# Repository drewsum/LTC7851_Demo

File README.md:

# LTC7851_Demo
Demo board for testing LTC7851 Quad Phase Buck Converter
KiCAD V5.0.0

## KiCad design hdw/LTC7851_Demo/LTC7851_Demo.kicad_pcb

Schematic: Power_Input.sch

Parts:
C201, C207: 0.1uF; C_0603; Voltage 50V; Digi-Key PN 490-4779-1-ND
C202, C205: 10nF; C_0603; Voltage 50V; Digi-Key PN 1276-1921-1-ND
C203: 1nF; C_0603; Voltage 50V; Digi-Key PN 311-1080-1-ND
C204, C206, C208: 100uF; CP_Tantalum_Case-X_EIA-7343-43_Reflow; Voltage 16V; Tolerance 10%; Digi-Key PN 718-1102-1-ND
D201: 24V; D_SMA; Digi-Key PN SMAJ24CALFCT-ND
D202: Green; LED_0603; Digi-Key PN 160-1446-1-ND
F201, F202: 25A; Fuse_SMD1206_Reflow; Digi-Key PN 507-1946-1-ND
J201: +12V IN; Wuerth_7461096_M4_Shank_9pos; Digi-Key PN 732-3214-ND
J206: GND IN; Wuerth_7461096_M4_Shank_9pos; Digi-Key PN 732-3214-ND
Q201, Q202: BSC123N10LSGATMA1; TDSON-8-1; Digi-Key PN BSC123N10LSGATMA1CT-ND
R201: 6.04M; R_0603; Tolerance 1%; Digi-Key PN 541-6.04MHCT-ND
R202: 86.6k; R_0603; Tolerance 1%; Digi-Key PN 311-86.6KHRCT-ND
R203: 243k; R_0603; Tolerance 1%; Digi-Key PN 541-243KHCT-ND
R204: 100k; R_0603; Tolerance 1%; Digi-Key PN P100KHCT-ND
R205, R206: 10; R_0603; Tolerance 1%; Digi-Key PN YAG3351CT-ND
R207: 10k; R_0603; Tolerance 1%; Digi-Key PN RHM10KADCT-ND
R208: 5.1k; R_0603; Tolerance 1%; Digi-Key PN RMCF0603FT5K10CT-ND
R209: 1k; R_0603; Tolerance 1%; Digi-Key PN RHM1.0KDCT-ND
TP201: TP; Pin_Header_Angled_1x01_Pitch2.54mm
TP202: TP; Measurement_Point_Round-SMD-Pad_Small
U201: LTC4365DDB; DFN-8-1EP_2x3mm_Pitch0.5mm; Digi-Key PN LTC4365IDDB#TRMPBFCT-ND
U202: 74LVC1G06; SOT-353_SC-70-5; Digi-Key PN 296-8484-1-ND

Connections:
+5.5V_MNG: C207.1, D202.2, R207.1, U202.5; also elsewhere on the board
+12V: C204.1, C206.1, C208.1, Q202.5 (D), TP202.1, U201.6; also elsewhere on the board
+12Vin: C201.1, C202.1, C203.1, D201.1, J201.1, Q201.5 (D), R201.1, R204.1, U201.4
GND: C201.2, C202.2, C203.2, C204.2, C205.2, C206.2, C207.2, C208.2, D201.2, J206.1, R203.2, TP201.1, U201.1, U201.9, U202.3; also elsewhere on the board
unnamed: C205.1, R208.2
unnamed: D202.1, R209.1
unnamed: Q201.1 (S), Q201.2 (S), Q201.3 (S), Q202.1 (S), Q202.2 (S), Q202.3 (S)
unnamed: Q201.4 (G), R205.2
unnamed: Q202.4 (G), R206.1
unnamed: R201.2, R202.1, U201.3
unnamed: R202.2, R203.1, U201.2
unnamed: R204.2, U201.8
unnamed: R205.1, R206.2, R208.1, U201.5
unnamed: R209.2, U202.4
POS12_PGOOD: R207.2, U201.7, U202.2

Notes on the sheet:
Power Input

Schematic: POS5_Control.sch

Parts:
C301, C302, C303, C304, C305: 0.1uF; C_0603; Voltage 50V; Digi-Key PN 490-4779-1-ND
D301: Red; LED_0603; Digi-Key PN 160-1447-1-ND
D302, D303: Green; LED_0603; Digi-Key PN 160-1446-1-ND
J301: CLKOUT; Pin_Header_Straight_1x02_Pitch2.54mm
J302: RUN; Pin_Header_Straight_1x03_Pitch2.54mm
J304: IAVG; Pin_Header_Straight_1x02_Pitch2.54mm
R301: 0; R_0603; Tolerance 1%; Digi-Key PN 311-0.0GRCT-ND
R302: 2; R_0603; Tolerance 1%; Digi-Key PN RMCF0603FT2R00CT-ND
R303: 51.1k; R_0603; Tolerance 1%; Digi-Key PN P51.1KHCT-ND
R304, R305, R310: 10k; R_0603; Tolerance 1%; Digi-Key PN RHM10KADCT-ND
R306, R307, R308: 1k; R_0603; Tolerance 1%; Digi-Key PN RHM1.0KDCT-ND
U301: LTC7851UHH; QFN-58-1EP_9x5mm_Pitch0.4mm; Digi-Key PN LTC7851IUHH#PBF-ND
U302: 74LVC1G17; SOT-353_SC-70-5; Digi-Key PN 296-11934-1-ND
U303, U304: 74LVC1G06; SOT-353_SC-70-5; Digi-Key PN 296-8484-1-ND

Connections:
+5.5V_MNG: C303.1, C304.1, C305.1, D301.2, D302.2, D303.2, J302.1, R301.1, R304.1, R305.1, U302.5, U303.5, U304.5; also elsewhere on the board
+12V: R302.1; also elsewhere on the board
/POS5 Phase 1/POS5_ISNS1_-: U301.45; also elsewhere on the board
/POS5 Phase 1/POS5_VSNSO1_-: U301.3; also elsewhere on the board
/POS5 Phase 2/POS5_ISNS2_-: U301.44; also elsewhere on the board
/POS5 Phase 3/POS5_ISNS3_-: U301.33; also elsewhere on the board
/POS5 Phase 4/POS5_ISNS4_-: U301.32; also elsewhere on the board
GND: C301.2, C302.2, C303.2, C304.2, C305.2, J301.2, J302.3, J304.2, R303.2, R310.2, U301.5, U301.59, U302.3, U303.3, U304.3; also elsewhere on the board
unnamed: C302.1, R302.2, U301.39
unnamed 21: U301.58; also elsewhere on the board
unnamed 25: U301.46; also elsewhere on the board
unnamed 29: U301.43; also elsewhere on the board
unnamed 33: U301.34; also elsewhere on the board
unnamed 37: U301.31; also elsewhere on the board
unnamed: D301.1, R306.1
unnamed: D302.1, R307.1
unnamed: D303.1, R308.1
unnamed: J301.1, U301.54
unnamed: R303.1, U301.56
unnamed: R306.2, U302.4
unnamed: R307.2, U303.4
unnamed: R308.2, U304.4
unnamed 75: U301.2; also elsewhere on the board
unnamed 80: U301.24; also elsewhere on the board
unnamed 81: U301.26; also elsewhere on the board
unnamed 82: U301.50; also elsewhere on the board
unnamed 83: U301.52; also elsewhere on the board
POS5_COMP: U301.1, U301.9, U301.13, U301.20; also elsewhere on the board
POS5_EXTVCC: C301.1, R301.2, U301.10, U301.11, U301.12, U301.21
POS5_IAVG: J304.1, U301.30, U301.35, U301.42, U301.47; also elsewhere on the board
POS5_ILIM: U301.29, U301.36, U301.41, U301.48; also elsewhere on the board
POS5_PGOOD_OC: R305.2, U301.25, U301.28, U301.38, U301.49, U304.2; also elsewhere on the board
POS5_RUN: J302.2, R310.1, U301.23, U301.27, U301.51, U301.53, U303.2
POS5_SS: U301.22, U301.37, U301.40, U301.57; also elsewhere on the board
POS5_VOSNS: U301.4, U301.6, U301.16, U301.17; also elsewhere on the board
~POS5_THDN: R304.2, U302.2; also elsewhere on the board

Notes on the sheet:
+5V Control

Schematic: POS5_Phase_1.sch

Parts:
C401, C402, C406: 100pF; C_0603; Voltage 50V; Digi-Key PN 490-4767-1-ND
C403: 3300pF; C_0603; Voltage 50V; Digi-Key PN 399-9066-1-ND
C404: 2200pF; C_0603; Voltage 50V; Digi-Key PN 490-4968-1-ND
C405, C407, C408, C410, C412, C420: 100uF; CP_Tantalum_Case-B_EIA-3528-21_Reflow; Voltage 6.3V; Tolerance 20%; Digi-Key PN 478-9994-1-ND
C409, C414: 1uF; C_0603; Voltage 16V; Digi-Key PN 1276-6524-1-ND
C411, C413: 0.1uF; C_0603; Voltage 50V; Digi-Key PN 490-4779-1-ND
C415: 0.22uF; C_0603; Voltage 50V; Digi-Key PN 490-5402-1-ND
C416, C418: 22uF; C_1210; Voltage 25V; Digi-Key PN 445-1436-1-ND
C417, C419: 100uF; C_1210; Voltage 10V; Digi-Key PN 587-3432-1-ND
L401: 0.47uH; L_Vishay_IHLP-4040; Tolerance 20%; Digi-Key PN 541-2595-1-ND
R401: 66.5k; R_0603; Tolerance 1%; Digi-Key PN RMCF0603FT66K5CT-ND
R402: 320; R_0603; Tolerance 1%; Digi-Key PN 541-4544-1-ND
R403: 6.04k; R_0603; Tolerance 1%; Digi-Key PN 311-6.04KHRCT-ND
R404: 10k; R_0603; Tolerance 1%; Digi-Key PN RHM10KADCT-ND
R405, R406: 2; R_0603; Tolerance 1%; Digi-Key PN RMCF0603FT2R00CT-ND
R407: 1.4k; R_0603; Tolerance 1%; Digi-Key PN P1.40KHCT-ND
R408: 0; R_0603; Tolerance 1%; Digi-Key PN 311-0.0GRCT-ND
R409: 10; R_0603; Tolerance 1%; Digi-Key PN YAG3351CT-ND
R410: 100k; R_0603; Tolerance 1%; Digi-Key PN P100KHCT-ND
R411: 13.7k; R_0603; Tolerance 1%; Digi-Key PN P13.7KHCT-ND
U301: LTC7851UHH; QFN-58-1EP_9x5mm_Pitch0.4mm; Digi-Key PN LTC7851IUHH#PBF-ND
U401: SiC779; MLP66-40_6x6mm_Pitch0.5mm; Digi-Key PN SIC779CD-T1-GE3CT-ND

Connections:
+5.5V_MNG: C409.1, R405.1, U401.3, U401.39; also elsewhere on the board
+5V: C405.1, C407.1, C408.1, C410.1, C412.1, C417.1, C419.1, C420.1, L401.2, R409.1; also elsewhere on the board
+12V: C414.1, C416.1, C418.1, U401.8, U401.9, U401.10, U401.11, U401.12, U401.13, U401.14, U401.P2; also elsewhere on the board
/POS5 Phase 1/POS5_ISNS1_+: R407.1; also elsewhere on the board
/POS5 Phase 1/POS5_ISNS1_-: C415.1, U301.45; also elsewhere on the board
/POS5 Phase 1/POS5_VSNSO1_+: R409.2, R410.1; also elsewhere on the board
/POS5 Phase 1/POS5_VSNSO1_-: R408.1, R411.2, U301.3
/POS5 Phase 2/POS5_ISNS2_-: U301.44; also elsewhere on the board
/POS5 Phase 3/POS5_ISNS3_-: U301.33; also elsewhere on the board
/POS5 Phase 4/POS5_ISNS4_-: U301.32; also elsewhere on the board
GND: C401.1, C402.1, C405.2, C407.2, C408.2, C409.2, C410.2, C411.2, C412.2, C414.2, C416.2, C417.2, C418.2, C419.2, C420.2, R401.2, R408.2, U301.5, U301.59, U401.5, U401.16, U401.17, U401.18, U401.19, U401.20, U401.21, U401.22, U401.23, U401.24, U401.25, U401.26, U401.27, U401.28, U401.37, U401.P1; also elsewhere on the board
unnamed 18: U301.39; also elsewhere on the board
unnamed: C403.2, R402.1
unnamed: C404.1, R403.2
unnamed: C404.2, C406.2, R402.2, R404.2, U301.58
unnamed: C411.1, R405.2, U401.2
unnamed: C413.1, R406.2
unnamed: C413.2, U401.7
unnamed: C415.2, R407.2, U301.46
unnamed 29: U301.43; also elsewhere on the board
unnamed 33: U301.34; also elsewhere on the board
unnamed 37: U301.31; also elsewhere on the board
unnamed 43: U301.54; also elsewhere on the board
unnamed 47: L401.1, U401.15, U401.29, U401.30, U401.31, U401.32, U401.33, U401.34, U401.35, U401.P3; also elsewhere on the board
unnamed 70: U301.56; also elsewhere on the board
unnamed: R406.1, U401.4
unnamed: R410.2, R411.1, U301.2
unnamed 80: U301.24; also elsewhere on the board
unnamed 81: U301.26; also elsewhere on the board
unnamed 82: U301.50; also elsewhere on the board
unnamed: U301.52, U401.40
POS5_COMP: C406.1, R403.1, U301.1, U301.9, U301.13, U301.20
POS5_EXTVCC: U301.10, U301.11, U301.12, U301.21; also elsewhere on the board
POS5_IAVG: C402.2, U301.30, U301.35, U301.42, U301.47; also elsewhere on the board
POS5_ILIM: R401.1, U301.29, U301.36, U301.41, U301.48
POS5_PGOOD_OC: U301.25, U301.28, U301.38, U301.49; also elsewhere on the board
POS5_RUN: U301.23, U301.27, U301.51, U301.53; also elsewhere on the board
POS5_SS: C401.2, U301.22, U301.37, U301.40, U301.57
POS5_VOSNS: C403.1, R404.1, U301.4, U301.6, U301.16, U301.17
~POS5_THDN: U401.38; also elsewhere on the board

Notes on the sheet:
Route as diff pairs
+5V Phase 1

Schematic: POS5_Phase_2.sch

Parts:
C501, C502, C503, C505, C507, C515: 100uF; CP_Tantalum_Case-B_EIA-3528-21_Reflow; Voltage 6.3V; Tolerance 20%; Digi-Key PN 478-9994-1-ND
C504: 1uF; C_0603_HandSoldering; Voltage 16V; Digi-Key PN 1276-6524-1-ND
C506, C508: 0.1uF; C_0603; Voltage 50V; Digi-Key PN 490-4779-1-ND
C509: 1uF; C_0603; Voltage 16V; Digi-Key PN 1276-6524-1-ND
C510: 0.22uF; C_0603; Voltage 50V; Digi-Key PN 490-5402-1-ND
C511, C513: 22uF; C_1210; Voltage 25V; Digi-Key PN 445-1436-1-ND
C512, C514: 100uF; C_1210; Voltage 10V; Digi-Key PN 587-3432-1-ND
L501: 0.47uH; L_Vishay_IHLP-4040; Tolerance 20%; Digi-Key PN 541-2595-1-ND
R501, R502: 2; R_0603; Tolerance 1%; Digi-Key PN RMCF0603FT2R00CT-ND
R503: 1.4k; R_0603; Tolerance 1%; Digi-Key PN P1.40KHCT-ND
U301: LTC7851UHH; QFN-58-1EP_9x5mm_Pitch0.4mm; Digi-Key PN LTC7851IUHH#PBF-ND
U501: SiC779; MLP66-40_6x6mm_Pitch0.5mm; Digi-Key PN SIC779CD-T1-GE3CT-ND

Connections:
+5.5V_MNG: C504.1, R501.1, U501.3, U501.39; also elsewhere on the board
+5V: C501.1, C502.1, C503.1, C505.1, C507.1, C512.1, C514.1, C515.1, L501.2; also elsewhere on the board
+12V: C509.1, C511.1, C513.1, U501.8, U501.9, U501.10, U501.11, U501.12, U501.13, U501.14, U501.P2; also elsewhere on the board
/POS5 Phase 1/POS5_ISNS1_-: U301.45; also elsewhere on the board
/POS5 Phase 1/POS5_VSNSO1_-: U301.3; also elsewhere on the board
/POS5 Phase 2/POS5_ISNS2_+: R503.1; also elsewhere on the board
/POS5 Phase 2/POS5_ISNS2_-: C510.1, U301.44; also elsewhere on the board
/POS5 Phase 3/POS5_ISNS3_-: U301.33; also elsewhere on the board
/POS5 Phase 4/POS5_ISNS4_-: U301.32; also elsewhere on the board
GND: C501.2, C502.2, C503.2, C504.2, C505.2, C506.2, C507.2, C509.2, C511.2, C512.2, C513.2, C514.2, C515.2, U301.5, U301.59, U501.5, U501.16, U501.17, U501.18, U501.19, U501.20, U501.21, U501.22, U501.23, U501.24, U501.25, U501.26, U501.27, U501.28, U501.37, U501.P1; also elsewhere on the board
unnamed 18: U301.39; also elsewhere on the board
unnamed 21: U301.58; also elsewhere on the board
unnamed 25: U301.46; also elsewhere on the board
unnamed: C506.1, R501.2, U501.2
unnamed: C508.1, R502.2
unnamed: C508.2, U501.7
unnamed: C510.2, R503.2, U301.43
unnamed 33: U301.34; also elsewhere on the board
unnamed 37: U301.31; also elsewhere on the board
unnamed 43: U301.54; also elsewhere on the board
unnamed 48: L501.1, U501.15, U501.29, U501.30, U501.31, U501.32, U501.33, U501.34, U501.35, U501.P3; also elsewhere on the board
unnamed 70: U301.56; also elsewhere on the board
unnamed 75: U301.2; also elsewhere on the board
unnamed: R502.1, U501.4
unnamed 80: U301.24; also elsewhere on the board
unnamed 81: U301.26; also elsewhere on the board
unnamed: U301.50, U501.40
unnamed 83: U301.52; also elsewhere on the board
POS5_COMP: U301.1, U301.9, U301.13, U301.20; also elsewhere on the board
POS5_EXTVCC: U301.10, U301.11, U301.12, U301.21; also elsewhere on the board
POS5_IAVG: U301.30, U301.35, U301.42, U301.47; also elsewhere on the board
POS5_ILIM: U301.29, U301.36, U301.41, U301.48; also elsewhere on the board
POS5_PGOOD_OC: U301.25, U301.28, U301.38, U301.49; also elsewhere on the board
POS5_RUN: U301.23, U301.27, U301.51, U301.53; also elsewhere on the board
POS5_SS: U301.22, U301.37, U301.40, U301.57; also elsewhere on the board
POS5_VOSNS: U301.4, U301.6, U301.16, U301.17; also elsewhere on the board
~POS5_THDN: U501.38; also elsewhere on the board

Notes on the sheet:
Route as diff pair
+5V Phase 2

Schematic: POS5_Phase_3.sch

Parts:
C601, C602, C603, C605, C607, C615: 100uF; CP_Tantalum_Case-B_EIA-3528-21_Reflow; Voltage 6.3V; Tolerance 20%; Digi-Key PN 478-9994-1-ND
C604, C609: 1uF; C_0603; Voltage 16V; Digi-Key PN 1276-6524-1-ND
C606, C608: 0.1uF; C_0603; Voltage 50V; Digi-Key PN 490-4779-1-ND
C610: 0.22uF; C_0603; Voltage 50V; Digi-Key PN 490-5402-1-ND
C611, C613: 22uF; C_1210; Voltage 25V; Digi-Key PN 445-1436-1-ND
C612, C614: 100uF; C_1210; Voltage 10V; Digi-Key PN 587-3432-1-ND
L601: 0.47uH; L_Vishay_IHLP-4040; Tolerance 20%; Digi-Key PN 541-2595-1-ND
R601, R602: 2; R_0603; Tolerance 1%; Digi-Key PN RMCF0603FT2R00CT-ND
R603: 1.4k; R_0603; Tolerance 1%; Digi-Key PN P1.40KHCT-ND
U301: LTC7851UHH; QFN-58-1EP_9x5mm_Pitch0.4mm; Digi-Key PN LTC7851IUHH#PBF-ND
U601: SiC779; MLP66-40_6x6mm_Pitch0.5mm; Digi-Key PN SIC779CD-T1-GE3CT-ND

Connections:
+5.5V_MNG: C604.1, R601.1, U601.3, U601.39; also elsewhere on the board
+5V: C601.1, C602.1, C603.1, C605.1, C607.1, C612.1, C614.1, C615.1, L601.2; also elsewhere on the board
+12V: C609.1, C611.1, C613.1, U601.8, U601.9, U601.10, U601.11, U601.12, U601.13, U601.14, U601.P2; also elsewhere on the board
/POS5 Phase 1/POS5_ISNS1_-: U301.45; also elsewhere on the board
/POS5 Phase 1/POS5_VSNSO1_-: U301.3; also elsewhere on the board
/POS5 Phase 2/POS5_ISNS2_-: U301.44; also elsewhere on the board
/POS5 Phase 3/POS5_ISNS3_+: R603.1; also elsewhere on the board
/POS5 Phase 3/POS5_ISNS3_-: C610.1, U301.33; also elsewhere on the board
/POS5 Phase 4/POS5_ISNS4_-: U301.32; also elsewhere on the board
GND: C601.2, C602.2, C603.2, C604.2, C605.2, C606.2, C607.2, C609.2, C611.2, C612.2, C613.2, C614.2, C615.2, U301.5, U301.59, U601.5, U601.16, U601.17, U601.18, U601.19, U601.20, U601.21, U601.22, U601.23, U601.24, U601.25, U601.26, U601.27, U601.28, U601.37, U601.P1; also elsewhere on the board
unnamed 18: U301.39; also elsewhere on the board
unnamed 21: U301.58; also elsewhere on the board
unnamed 25: U301.46; also elsewhere on the board
unnamed 29: U301.43; also elsewhere on the board
unnamed: C606.1, R601.2, U601.2
unnamed: C608.1, R602.2
unnamed: C608.2, U601.7
unnamed: C610.2, R603.2, U301.34
unnamed 37: U301.31; also elsewhere on the board
unnamed 43: U301.54; also elsewhere on the board
unnamed 49: L601.1, U601.15, U601.29, U601.30, U601.31, U601.32, U601.33, U601.34, U601.35, U601.P3; also elsewhere on the board
unnamed 70: U301.56; also elsewhere on the board
unnamed 75: U301.2; also elsewhere on the board
unnamed: R602.1, U601.4
unnamed 80: U301.24; also elsewhere on the board
unnamed: U301.26, U601.40
unnamed 82: U301.50; also elsewhere on the board
unnamed 83: U301.52; also elsewhere on the board
POS5_COMP: U301.1, U301.9, U301.13, U301.20; also elsewhere on the board
POS5_EXTVCC: U301.10, U301.11, U301.12, U301.21; also elsewhere on the board
POS5_IAVG: U301.30, U301.35, U301.42, U301.47; also elsewhere on the board
POS5_ILIM: U301.29, U301.36, U301.41, U301.48; also elsewhere on the board
POS5_PGOOD_OC: U301.25, U301.28, U301.38, U301.49; also elsewhere on the board
POS5_RUN: U301.23, U301.27, U301.51, U301.53; also elsewhere on the board
POS5_SS: U301.22, U301.37, U301.40, U301.57; also elsewhere on the board
POS5_VOSNS: U301.4, U301.6, U301.16, U301.17; also elsewhere on the board
~POS5_THDN: U601.38; also elsewhere on the board

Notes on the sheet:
Route as diff pair
+5V Phase 3

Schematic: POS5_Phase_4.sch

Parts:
C701, C702, C703, C705, C707, C715: 100uF; CP_Tantalum_Case-B_EIA-3528-21_Reflow; Voltage 6.3V; Tolerance 20%; Digi-Key PN 478-9994-1-ND
C704, C709: 1uF; C_0603; Voltage 16V; Digi-Key PN 1276-6524-1-ND
C706, C708: 0.1uF; C_0603; Voltage 50V; Digi-Key PN 490-4779-1-ND
C710: 0.22uF; C_0603; Voltage 50V; Digi-Key PN 490-5402-1-ND
C711, C713: 22uF; C_1210; Voltage 25V; Digi-Key PN 445-1436-1-ND
C712, C714: 100uF; C_1210; Voltage 10V; Digi-Key PN 587-3432-1-ND
L701: 0.47uH; L_Vishay_IHLP-4040; Tolerance 20%; Digi-Key PN 541-2595-1-ND
R701, R702: 2; R_0603; Tolerance 1%; Digi-Key PN RMCF0603FT2R00CT-ND
R703: 1.4k; R_0603; Tolerance 1%; Digi-Key PN P1.40KHCT-ND
U301: LTC7851UHH; QFN-58-1EP_9x5mm_Pitch0.4mm; Digi-Key PN LTC7851IUHH#PBF-ND
U701: SiC779; MLP66-40_6x6mm_Pitch0.5mm; Digi-Key PN SIC779CD-T1-GE3CT-ND

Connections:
+5.5V_MNG: C704.1, R701.1, U701.3, U701.39; also elsewhere on the board
+5V: C701.1, C702.1, C703.1, C705.1, C707.1, C712.1, C714.1, C715.1, L701.2; also elsewhere on the board
+12V: C709.1, C711.1, C713.1, U701.8, U701.9, U701.10, U701.11, U701.12, U701.13, U701.14, U701.P2; also elsewhere on the board
/POS5 Phase 1/POS5_ISNS1_-: U301.45; also elsewhere on the board
/POS5 Phase 1/POS5_VSNSO1_-: U301.3; also elsewhere on the board
/POS5 Phase 2/POS5_ISNS2_-: U301.44; also elsewhere on the board
/POS5 Phase 3/POS5_ISNS3_-: U301.33; also elsewhere on the board
/POS5 Phase 4/POS5_ISNS4_+: R703.1; also elsewhere on the board
/POS5 Phase 4/POS5_ISNS4_-: C710.1, U301.32; also elsewhere on the board
GND: C701.2, C702.2, C703.2, C704.2, C705.2, C706.2, C707.2, C709.2, C711.2, C712.2, C713.2, C714.2, C715.2, U301.5, U301.59, U701.5, U701.16, U701.17, U701.18, U701.19, U701.20, U701.21, U701.22, U701.23, U701.24, U701.25, U701.26, U701.27, U701.28, U701.37, U701.P1; also elsewhere on the board
unnamed 18: U301.39; also elsewhere on the board
unnamed 21: U301.58; also elsewhere on the board
unnamed 25: U301.46; also elsewhere on the board
unnamed 29: U301.43; also elsewhere on the board
unnamed 33: U301.34; also elsewhere on the board
unnamed: C706.1, R701.2, U701.2
unnamed: C708.1, R702.2
unnamed: C708.2, U701.7
unnamed: C710.2, R703.2, U301.31
unnamed 43: U301.54; also elsewhere on the board
unnamed 50: L701.1, U701.15, U701.29, U701.30, U701.31, U701.32, U701.33, U701.34, U701.35, U701.P3; also elsewhere on the board
unnamed 70: U301.56; also elsewhere on the board
unnamed 75: U301.2; also elsewhere on the board
unnamed: R702.1, U701.4
unnamed: U301.24, U701.40
unnamed 81: U301.26; also elsewhere on the board
unnamed 82: U301.50; also elsewhere on the board
unnamed 83: U301.52; also elsewhere on the board
POS5_COMP: U301.1, U301.9, U301.13, U301.20; also elsewhere on the board
POS5_EXTVCC: U301.10, U301.11, U301.12, U301.21; also elsewhere on the board
POS5_IAVG: U301.30, U301.35, U301.42, U301.47; also elsewhere on the board
POS5_ILIM: U301.29, U301.36, U301.41, U301.48; also elsewhere on the board
POS5_PGOOD_OC: U301.25, U301.28, U301.38, U301.49; also elsewhere on the board
POS5_RUN: U301.23, U301.27, U301.51, U301.53; also elsewhere on the board
POS5_SS: U301.22, U301.37, U301.40, U301.57; also elsewhere on the board
POS5_VOSNS: U301.4, U301.6, U301.16, U301.17; also elsewhere on the board
~POS5_THDN: U701.38; also elsewhere on the board

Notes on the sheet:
Route as diff pair
+5V Phase 4

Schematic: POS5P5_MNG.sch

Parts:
C801: 10uF; CP_Tantalum_Case-B_EIA-3528-21_Reflow; Voltage 16V; Tolerance 10%; Digi-Key PN 399-5034-1-ND
C802, C803, C804: 0.1uF; C_0603; Voltage 50V; Digi-Key PN 490-4779-1-ND
C805: 100uF; CP_Tantalum_Case-B_EIA-3528-21_Reflow; Voltage 6.3V; Tolerance 20%; Digi-Key PN 478-9994-1-ND
R801: 200; R_0603; Tolerance 1%; Digi-Key PN MCT0603-200-CFCT-ND
R802: 680; R_0603; Tolerance 1%; Digi-Key PN P680HCT-ND
TP801: TP; Measurement_Point_Round-SMD-Pad_Small
U801: LM1117-ADJ; SOT-223-3_TabPin2; Digi-Key PN LM1117IMPX-ADJ/NOPBCT-ND

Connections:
+5.5V_MNG: C804.1, C805.1, R801.1, TP801.1, U801.2; also elsewhere on the board
+12V: C801.1, C802.1, U801.3; also elsewhere on the board
GND: C801.2, C802.2, C803.2, C804.2, C805.2, R802.2; also elsewhere on the board
unnamed: C803.1, R801.2, R802.1, U801.1

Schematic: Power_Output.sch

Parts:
J901, J902: +5V OUT; Wuerth_7461096_M4_Shank_9pos; Digi-Key PN 732-3214-ND
J903, J904: GND OUT; Wuerth_7461096_M4_Shank_9pos; Digi-Key PN 732-3214-ND

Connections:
+5V: J901.1, J902.1; also elsewhere on the board
GND: J903.1, J904.1; also elsewhere on the board

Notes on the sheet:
Place bulk output caps close to terminals

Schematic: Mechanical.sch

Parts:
MH1001, MH1002, MH1005, MH1006: MountingHole; MountingHole_3mm
MK1001, MK1002, MK1009, MK1010: 4-40 Screw; Digi-Key PN 36-9900-ND
MK1003, MK1004, MK1011, MK1012: 4-40 Standoff; Digi-Key PN 36-8400-ND

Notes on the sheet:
Mounting Holes and Mechanical Components

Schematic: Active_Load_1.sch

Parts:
C1101: 1uF; C_0603; Voltage 16V; Digi-Key PN 1276-6524-1-ND
C1102: 0.1uF; C_0603; Voltage 50V; Digi-Key PN 490-4779-1-ND
C1103: 10uF; CP_Tantalum_Case-B_EIA-3528-21_Reflow; Voltage 16V; Tolerance 10%; Digi-Key PN 399-5034-1-ND
J1101: FG_LOAD; Pin_Header_Straight_1x02_Pitch2.54mm
J1102: ISNS; Pin_Header_Straight_1x02_Pitch2.54mm
Q1101, Q1102: BSC123N10LSGATMA1; TDSON-8-1; Digi-Key PN BSC123N10LSGATMA1CT-ND
R1101, R1105, R1106: 10k; R_0603; Tolerance 1%; Digi-Key PN RHM10KADCT-ND
R1102, R1103, R1104: 10; R_0603; Tolerance 1%; Digi-Key PN YAG3351CT-ND
R1107, R1108: 5m; R_2512; Tolerance 1%; Digi-Key PN YAG2145CT-ND
U1101: LT1010DD; DFN-8-1EP_3x3mm_Pitch0.5mm; Digi-Key PN LT1010CDD#PBF-ND

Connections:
+5V: Q1101.5 (D), Q1102.5 (D); also elsewhere on the board
+12V: C1101.1, C1102.1, C1103.1, R1102.1, U1101.1; also elsewhere on the board
GND: C1101.2, C1102.2, C1103.2, J1101.2, J1102.2, R1101.2, R1105.2, R1106.2, R1107.2, R1108.2, U1101.6, U1101.9; also elsewhere on the board
LOAD_GATE: R1103.2, R1104.2, U1101.3; also elsewhere on the board
unnamed: J1101.1, R1101.1, U1101.8
unnamed: J1102.1, Q1101.1 (S), Q1101.2 (S), Q1101.3 (S), R1107.1
unnamed: Q1101.4 (G), R1103.1, R1105.1
unnamed: Q1102.1 (S), Q1102.2 (S), Q1102.3 (S), R1108.1
unnamed: Q1102.4 (G), R1104.1, R1106.1
unnamed: R1102.2, U1101.2

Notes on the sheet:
Active Load Driver and Active Load Bank 1

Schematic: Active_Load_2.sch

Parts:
Q1201, Q1202: BSC123N10LSGATMA1; TDSON-8-1; Digi-Key PN BSC123N10LSGATMA1CT-ND
R1201, R1202: 10; R_0603; Tolerance 1%; Digi-Key PN YAG3351CT-ND
R1203, R1204: 10k; R_0603; Tolerance 1%; Digi-Key PN RHM10KADCT-ND
R1205, R1206: 5m; R_2512; Tolerance 1%; Digi-Key PN YAG2145CT-ND

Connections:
+5V: Q1201.5 (D), Q1202.5 (D); also elsewhere on the board
GND: R1203.2, R1204.2, R1205.2, R1206.2; also elsewhere on the board
LOAD_GATE: R1201.2, R1202.2; also elsewhere on the board
unnamed: Q1201.1 (S), Q1201.2 (S), Q1201.3 (S), R1205.1
unnamed: Q1201.4 (G), R1201.1, R1203.1
unnamed: Q1202.1 (S), Q1202.2 (S), Q1202.3 (S), R1206.1
unnamed: Q1202.4 (G), R1202.1, R1204.1

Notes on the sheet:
Active Load Bank 2

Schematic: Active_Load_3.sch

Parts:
Q1301, Q1302: BSC123N10LSGATMA1; TDSON-8-1; Digi-Key PN BSC123N10LSGATMA1CT-ND
R1301, R1302: 10; R_0603; Tolerance 1%; Digi-Key PN YAG3351CT-ND
R1303, R1304: 10k; R_0603; Tolerance 1%; Digi-Key PN RHM10KADCT-ND
R1305, R1306: 5m; R_2512; Tolerance 1%; Digi-Key PN YAG2145CT-ND

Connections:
+5V: Q1301.5 (D), Q1302.5 (D); also elsewhere on the board
GND: R1303.2, R1304.2, R1305.2, R1306.2; also elsewhere on the board
LOAD_GATE: R1301.2, R1302.2; also elsewhere on the board
unnamed: Q1301.1 (S), Q1301.2 (S), Q1301.3 (S), R1305.1
unnamed: Q1301.4 (G), R1301.1, R1303.1
unnamed: Q1302.1 (S), Q1302.2 (S), Q1302.3 (S), R1306.1
unnamed: Q1302.4 (G), R1302.1, R1304.1

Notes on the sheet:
Active Load Bank 3

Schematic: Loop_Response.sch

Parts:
J1401: VOUT; Pin_Header_Straight_1x02_Pitch2.54mm
J1402: LOOP_TAP; Pin_Header_Straight_1x02_Pitch2.54mm
J1403: Wave_Gen_In; Pin_Header_Straight_1x02_Pitch2.54mm
T1401: 1:1 Pulse Transformer; Murata_78601_9C; Digi-Key PN 811-2650-ND

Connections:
+5V: J1401.1, T1401.4; also elsewhere on the board
GND: J1401.2, J1402.2, J1403.2, T1401.2; also elsewhere on the board
LOOP_TAP: J1402.1, T1401.3; also elsewhere on the board
unnamed: J1403.1, T1401.1

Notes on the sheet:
Open Loop Transfer Function Test Components

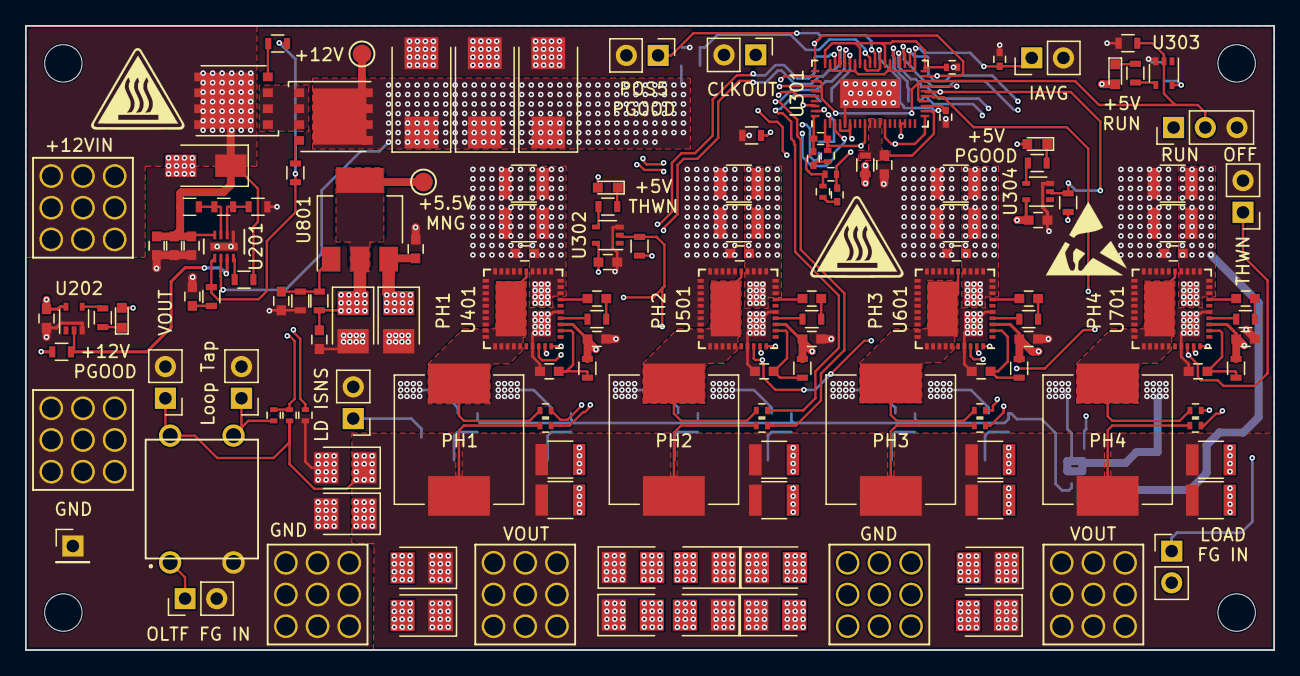
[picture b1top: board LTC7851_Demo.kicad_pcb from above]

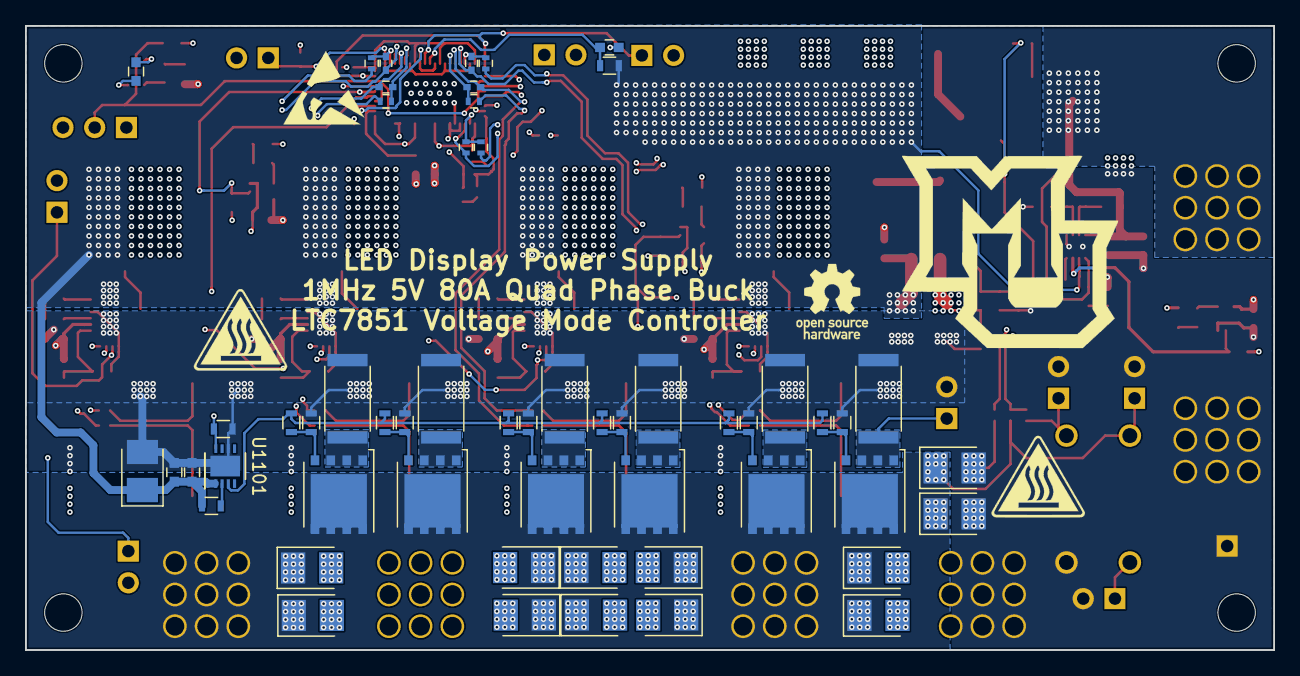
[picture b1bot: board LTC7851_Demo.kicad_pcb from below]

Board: 4 copper layers, 100.0 x 50.0 mm, 208 parts (55 on the bottom side), 94 nets.

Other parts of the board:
J303: THDN; Pin_Header_Straight_1x02_Pitch2.54mm
J305: PGOOD; Pin_Header_Straight_1x02_Pitch2.54mm
MH1003, MH1004: MountingHole; MountingHole_3mm
R412, R413, R414, R504, R505, R604, R605, R704, R705: 0; R_0402

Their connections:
+5V: R413.2, R505.2, R605.2, R705.2; also elsewhere on the board
/POS5 Phase 1/POS5_ISNS1_+: R412.1; also elsewhere on the board
/POS5 Phase 1/POS5_ISNS1_-: R413.1; also elsewhere on the board
/POS5 Phase 1/POS5_VSNSO1_+: R414.2; also elsewhere on the board
/POS5 Phase 2/POS5_ISNS2_+: R504.1; also elsewhere on the board
/POS5 Phase 2/POS5_ISNS2_-: R505.1; also elsewhere on the board
/POS5 Phase 3/POS5_ISNS3_+: R604.1; also elsewhere on the board
/POS5 Phase 3/POS5_ISNS3_-: R605.1; also elsewhere on the board
/POS5 Phase 4/POS5_ISNS4_+: R704.1; also elsewhere on the board
/POS5 Phase 4/POS5_ISNS4_-: R705.1; also elsewhere on the board
GND: J303.2, J305.2; also elsewhere on the board
LOOP_TAP: R414.1; also elsewhere on the board
unnamed 47: R412.2; also elsewhere on the board
unnamed 48: R504.2; also elsewhere on the board
unnamed 49: R604.2; also elsewhere on the board
unnamed 50: R704.2; also elsewhere on the board
POS5_PGOOD_OC: J305.1; also elsewhere on the board
~POS5_THDN: J303.1; also elsewhere on the board

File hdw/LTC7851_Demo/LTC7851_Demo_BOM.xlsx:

References | Value | Quantity Per PCB | Digi-Key PN | Footprint
C207 C301 C302 C303 C304 C305 C411 C413 C506 C508 C606 C608 C706 C708 C802 C803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 | 0.1uF | 18 | 490-4779-1-ND | 603
C201 | 0.1uF | 1 | 490-4779-1-ND | 603
C415 C510 C610 C710 | 0.22uF | 4 | 490-5402-1-ND | 603
C401 C402 C406 | 100pF | 3 | 490-4767-1-ND | 603
C204 C206 C208 | 100uF | 3 | 718-1102-1-ND | 7343
C405 C407 C408 C410 C412 C420 C501 C502 C503 C505 C507 C515 C601 C602 C603 C605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 | 100uF | 25 | 478-9994-1-ND | 3528
C417 C419 C512 C514 C612 C614 C712 C714 | 100uF | 8 | 587-3432-1-ND | 1210
C202 C205 | 10nF | 2 | 1276-1921-1-ND | 603
C801 C1103 | 10uF | 2 | 399-5034-1-ND | 3528
C203 | 1nF | 1 | 311-1080-1-ND | 603
C409 C414 C509 C604 C609 C704 C709 C1101 | 1uF | 8 | 1276-6524-1-ND | 603
C504 | 1uF | 1 | 1276-6524-1-ND | 603
C404 | 2200pF | 1 | 490-4968-1-ND | 603
C416 C418 C511 C513 C611 C613 C711 C713 | 22uF | 8 | 445-1436-1-ND | 1210
C403 | 3300pF | 1 | 399-9066-1-ND | 603
D201 | 24V | 1 | SMAJ24CALFCT-ND
D202 D302 D303 | Green | 3 | 160-1446-1-ND
D301 | Red | 1 | 160-1447-1-ND
F201 F202 | 25A | 2 | 507-1946-1-ND
J201 | +12V IN | 1 | 732-3214-ND
J901 J902 | +5V OUT | 2 | 732-3214-ND
J301 | CLKOUT | 1
J1101 | FG_LOAD | 1
J206 | GND IN | 1 | 732-3214-ND
J903 J904 | GND OUT | 2 | 732-3214-ND
J304 | IAVG | 1
J1102 | ISNS | 1
J1402 | LOOP_TAP | 1
J302 | RUN | 1
J1401 | VOUT | 1
J1403 | Wave_Gen_In | 1
L401 L501 L601 L701 | 0.47uH | 4 | 541-2595-1-ND | IHLP4040
MK1001 MK1002 MK1009 MK1010 | 4-40 Screw | 4 | 36-9900-ND
MK1003 MK1004 MK1011 MK1012 | 4-40 Standoff | 4 | 36-8400-ND
Q201 Q202 Q1101 Q1102 Q1201 Q1202 Q1301 Q1302 | BSC123N10LSGATMA1 | 8 | BSC123N10LSGATMA1CT-ND
R301 R408 | 0 | 2 | 311-0.0GRCT-ND | 603
R407 R503 R603 R703 | 1.4k | 4 | P1.40KHCT-ND | 603
R205 R206 R409 R1102 R1103 R1104 R1201 R1202 R1301 R1302 | 10 | 10 | YAG3351CT-ND | 603
R204 R410 | 100k | 2 | P100KHCT-ND | 603
R207 R304 R305 R310 R404 R1101 R1105 R1106 R1203 R1204 R1303 R1304 | 10k | 12 | RHM10KADCT-ND | 603
R411 | 13.7k | 1 | P13.7KHCT-ND | 603
R209 R306 R307 R308 | 1k | 4 | RHM1.0KDCT-ND | 603
R302 R405 R406 R501 R502 R601 R602 R701 R702 | 2 | 9 | RMCF0603FT2R00CT-ND | 603
R801 | 200 | 1 | MCT0603-200-CFCT-ND | 603
R203 | 243k | 1 | 541-243KHCT-ND | 603
R402 | 320 | 1 | 541-4544-1-ND | 603
R208 | 5.1k | 1 | RMCF0603FT5K10CT-ND | 603
R303 | 51.1k | 1 | P51.1KHCT-ND | 603
R1107 R1108 R1205 R1206 R1305 R1306 | 5m | 6 | YAG2145CT-ND | 2512
R201 | 6.04M | 1 | 541-6.04MHCT-ND | 603
R403 | 6.04k | 1 | 311-6.04KHRCT-ND | 603
R401 | 66.5k | 1 | RMCF0603FT66K5CT-ND | 603
R802 | 680 | 1 | P680HCT-ND | 603
R202 | 86.6k | 1 | 311-86.6KHRCT-ND | 603
T1401 | 1:1 Pulse Transformer | 1 | 811-2650-ND
U202 U303 U304 | 74LVC1G06 | 3 | 296-8484-1-ND
U302 | 74LVC1G17 | 1 | 296-11934-1-ND
U801 | LM1117-ADJ | 1 | LM1117IMPX-ADJ/NOPBCT-ND
U1101 | LT1010DD | 1 | LT1010CDD#PBF-ND
U201 | LTC4365DDB | 1 | LTC4365IDDB#TRMPBFCT-ND
U301 | LTC7851UHH | 1 | LTC7851IUHH#PBF-ND
U401 U501 U601 U701 | SiC779 | 4 | SIC779CD-T1-GE3CT-ND

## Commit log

2018-10-04 Added kicad project
2018-10-05 Populated Phase 1 page
2018-10-06 Added LDO for VCC input, cleaned some stuff up
2018-10-10 Added blank active load pages
2018-10-11 Added active load sheets
2018-10-11 Removed extra active load sheet
2018-10-12 Added component values for all phase 1 components
2018-10-13 Duplicated master phase, added status LEDs and a few test points
2018-10-13 Filled in power input page
2018-10-14 Assigned some custom footprints
2018-10-14 Annotated schematic
2018-10-14 Cleaned up for ERC
2018-10-14 Changed cap voltage rating
2018-10-14 Added Digi-Key part numbers for all parts
2018-10-14 edited .gitignore
2018-10-14 Assigned footprints
2018-10-14 Added page titles
2018-10-14 Added design rules, layer setup
2018-10-14 Board outline, mounting holes placed
2018-10-14 Arranged components for phase 1
2018-10-14 Duplicated phase 1 four times and changed ref des
2018-10-14 Placed phases on board
2018-10-14 Finished arranging parts on board
2018-10-14 Flipped order of phases on PCB
2018-10-14 Flipped phases again, better order now
2018-10-14 Added GND plane
2018-10-14 More routing
2018-10-16 Added KiCad version info to readme.md
2018-10-16 A lot more power flooding
2018-10-16 revising power vias
2018-10-17 Routed current sense and voltage sense
2018-10-17 Routed PWM
2018-10-17 Routed some garbage near the controller
2018-10-17 More routing, removed GL ang GH phase test points
2018-10-17 Resolved mounting hole ref des issue
2018-10-17 More routing, silkscreen labels
2018-10-18 Finished ROUTING (for the most part)
2018-10-18 Finished routing, added 3D render png, ordered PCB
2018-10-25 Added a few connectors and cleaned up some routing
2018-10-31 Substantial wiring and layout changes
2018-11-01 Furthe rrouting refinements
2018-11-03 Finished routing and added 3D renders
